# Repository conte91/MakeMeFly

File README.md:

This is a Programmable magnetic levitation project for my Electronics for embedded system course @Polythecnic University of Torino.

Follow my blog http://tux4u.wordpress.com for news about the project!

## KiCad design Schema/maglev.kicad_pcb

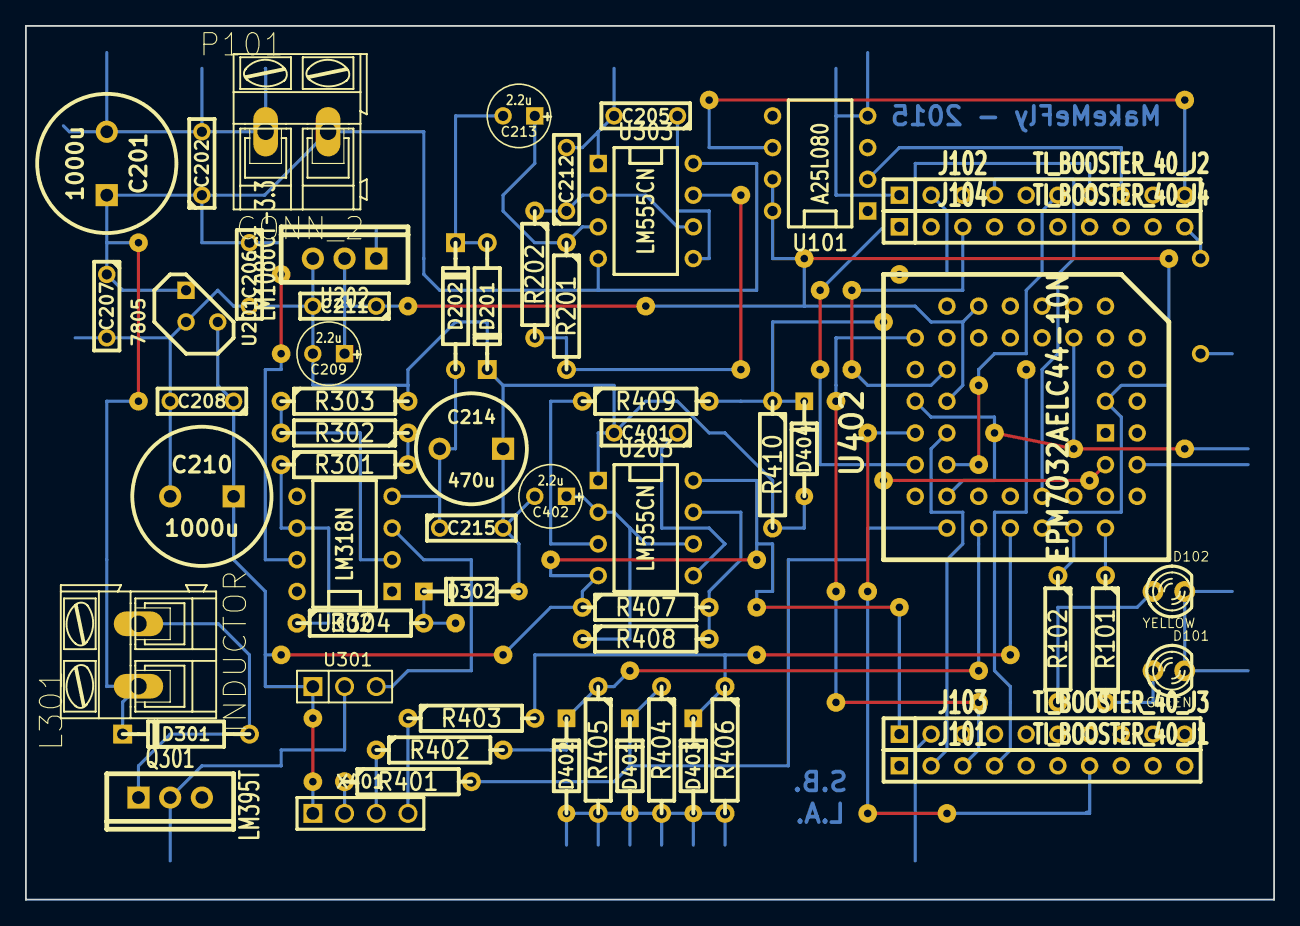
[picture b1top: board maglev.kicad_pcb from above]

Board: 2 copper layers, 100.0 x 70.0 mm, 60 parts (1 on the bottom side), 47 nets.

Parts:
C201, C210: 1000u; C2V10
C202, C205, C206, C207, C208, C211, C215: 100n; C2
C209, C213, C402: 2.2u; C1V5
C212, C401: 4.7n; C2
C214: 470u; C2V8
D101: GREEN; LED-3MM
D102: YELLOW; LED-3MM
D201, D202, D301: 1N4007; DO-41
D302, D401, D402, D403, D404: 1N5226B; DO-35
J101: TI_BOOSTER_40_J1; SIL-10
J102: TI_BOOSTER_40_J2; SIL-10
J103: TI_BOOSTER_40_J3; SIL-10
J104: TI_BOOSTER_40_J4; SIL-10
L301: INDUCTOR; AK300-2
P101: CONN_2; AK300-2
Q301: LM395T; TO220_VERT_123
R101, R102, R304, R401, R402, R403, R409: 100; R4
R201: 3.3k; R4
R202, R303, R404, R405, R406, R408, R410: 10k; R4
R301, R302: 1k; R4
R407: 2.2k; R4
SW101: SW_PUSH; R3
U101: A25L080; DIP-8__300
U201: 7805; LM78XX-TO92
U202: LM1086CT-3.3; TO220_VERT_123
U203, U303: LM555CN; DIP-8__300
U301: SS495; PIN_ARRAY_3X1
U302: LM318N; DIP-8__300
U402: EPM7032AELC44-10N; PLCC44
X401: MOUSE_BUTTON_IF; PIN_ARRAY_4x1

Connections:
3.3V: C209.1, C211.1, U101.7, U101.8, U202.2, U402.3, U402.15, U402.23, U402.35
5V: C208.1, C210.1, J103.1, R407.1, U201.VO, U203.4, U203.8, U301.1, X401.1
12V: C201.1, C202.1, C206.1, C207.1, D301.2, L301.1, P101.2, U201.VI, U202.3, U302.7, U303.4, U303.8
-12V: C214.2, C215.1, D202.1, U302.4
/CS: J101.10, U101.1
/Mouse_input_control/D0: J101.3, U402.18
/Mouse_input_control/D1: J101.4, U402.19
/Mouse_input_control/D2: J102.2, U402.20
/Mouse_input_control/D3: J104.3, U402.21
/Mouse_input_control/D4: J101.7, U402.24
/Mouse_input_control/D5: J101.2, U402.25
/Mouse_input_control/D6: J102.7, U402.26
/Mouse_input_control/D7: J102.6, U402.27
/Mouse_input_control/OVERFLOW: R101.1, U402.39
/Mouse_input_control/RST: J102.4, U402.36
/Mouse_input_control/UNDERFLOW: R102.1, U402.37
B_SENSE: D302.2, J103.9, R304.2
GND: C201.2, C202.2, C205.2, C206.2, C207.2, C208.2, C209.2, C210.2, C211.2, C212.2, C214.1, C215.2, C401.2, C402.2, D101.2, D102.2, D201.2, D302.1, D401.1, D402.1, D403.1, D404.1, J102.1, J103.2, P101.1, Q301.2, R303.2, R404.2, R405.2, R406.2, R410.2, SW101.1, U101.4, U201.GND, U202.1, U203.1, U301.2, U303.1, U402.10, U402.22, U402.30, U402.42
MISO: J102.8, U101.2
MOSI: J101.8, U101.5
unnamed: J104.10, SW101.2
unnamed: D101.1, R101.2
unnamed: D102.1, R102.2
unnamed: C212.1, R202.1, U303.2, U303.6
unnamed: R201.2, R202.2, U303.7
unnamed: C213.2, D201.1, D202.2
unnamed: C213.1, R201.1, U303.3
unnamed: C205.1, U303.5
unnamed: R302.2, R303.1, U302.2
unnamed: R301.2, R302.1
unnamed: D301.1, L301.2, Q301.3
unnamed: U301.3, U302.3
unnamed: R301.1, R304.1, U302.6
unnamed: R403.1, X401.4
unnamed: C401.1, U203.5
unnamed: D403.2, R403.2, R406.1, U402.33
unnamed: D402.2, R402.2, R405.1, U402.31
unnamed: D401.2, R401.2, R404.1, U402.29
unnamed: R402.1, X401.3
unnamed: R401.1, X401.2
unnamed: C402.1, R408.1, U203.2, U203.6
unnamed: R409.1, U203.3
unnamed: D404.2, R409.2, R410.1, U402.43
unnamed: R407.2, R408.2, U203.7
PWR_OUT: J104.2, Q301.1
SPICLK: J102.10, U101.6
WEN: J101.9, U101.3

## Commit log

2014-03-23 Readme
2014-03-23 Useful git libraries
2014-03-23 gitignore
2014-03-23 move CBuf
2014-03-23 First ADC test
2014-03-23 Code cleanup
2014-03-23 Publisher from serial to ROS
2015-08-22 PWM test to check sensor readings for different magnetic fields
2015-08-27 Various control tries
2015-08-27 1-second yeeeeah :D
2015-08-31 Stellaris wins, Magnet floats!!
2015-09-07 Tanti giorni di lavoro andati a buon fine :)
2015-09-15 Sure it works now :)
2015-09-15 Report
2015-09-15 Add licensing information
2015-09-15 Fix and optimize CPLD architecture - RTL wins, behavioural loses
2015-09-15 Add some informations about CPLD and more details on power DAC output
2015-09-24 Plotter is workin now :)
2015-12-20 Update submodules
